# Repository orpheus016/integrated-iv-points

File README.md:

# four-point-probe
Four point probe for semiconductor instrumentation system

## Software: voltage simulation pipeline

This repo includes a modular Python simulation for voltage acquisition with
filters, live plotting, and CSV logging. It is designed to be swapped later with
ADS1256 serial input from Arduino.

## Development

If you plan to change code, start with:

- [CONTRIBUTING.md](CONTRIBUTING.md) for the CI contract, local preflight, and PR checklist.
- [software/scripts/README.md](software/scripts/README.md) for `evaluate`, `integrate`, and the compliance checker.
- [software/README.md](software/README.md) for the software module overview and run examples.
- `CONTRIBUTING.md` also explains how to write new tests under `software/tests/` and run them from the repo root.

### Setup

Install dependencies:

```bash
pip install matplotlib
```

Optional (for future ADS1256 serial input):

```bash
pip install pyserial
```

### Run

From the repo root:

```bash
python -m software.main
```

Example with custom settings:

```bash
python -m software.main --sample-rate 100 --window-seconds 8 --noise 0.0005 --step
```

## Offline data paths

There are two ways to work with recorded CSV data:

1. Replay a CSV through the live runtime when you want the same pipeline as hardware, including the backbone, logger, and visualizer:

```bash
python -m software.main --source csv --csv-path software/output/testbench/stable20mA.csv --backbone baseline
```

2. Run offline evaluation when you want metrics and snapshot comparison without hardware commands or the live plot loop:

```bash
python -m software.scripts.evaluate --input software/output/testbench/stable20mA.csv --backbones baseline --out software/output/evaluate/baseline-stable20mA
```

The offline evaluator writes a metrics CSV with the decided snapshot fields, marks that chosen snapshot with a star in the plot, and keeps the result separate from the live runtime output.

The default snapshot recording gate is configured in [software/config/config.py](software/config/config.py), including the minimum recording duration used before a backbone may decide on a VI snapshot.

## Serial protocol and CLI

Hardware integration uses a small text protocol implemented by the Arduino firmware and
managed by `software/command/serial_commander.py`.

Framing markers (exact strings):

- `*STREAM_START` — emitted by the Arduino to mark stream beginning
- `*STREAM_STOP` — emitted by the Arduino to mark stream termination

Control commands sent from host to Arduino (single ASCII characters):

- `R` — reset device
- `C` — start streaming samples
- `s` — stop streaming
- `iN` — set current stage to `N` (e.g. `i2`)

The serial reader expects CSV-style measurement lines containing `voltage,current_mA`.

Common CLI execution examples:

- Replay testbench CSVs and write evaluation results:
	python -m software.scripts.evaluate --input software/output/testbench --out results/

Single backbone on single dataset (example):
	python -m software.scripts.evaluate \
		--input software/output/testbench/stable20mA.csv \
		--backbones baseline \
		--out results/single_baseline_stable20mA
- Run main with hardware ADS1256 on COM5:
	python -m software.main --source serial --port COM5 --baud 115200 --backbone baseline
- Run headless evaluation from Python:
	python -c "from software.scripts.evaluate import main; main(['--input','software/output/testbench'])"

See `software/config/config.py` for all CLI defaults and flags (backbone selection, hysteresis thresholds, plot mode, etc.).

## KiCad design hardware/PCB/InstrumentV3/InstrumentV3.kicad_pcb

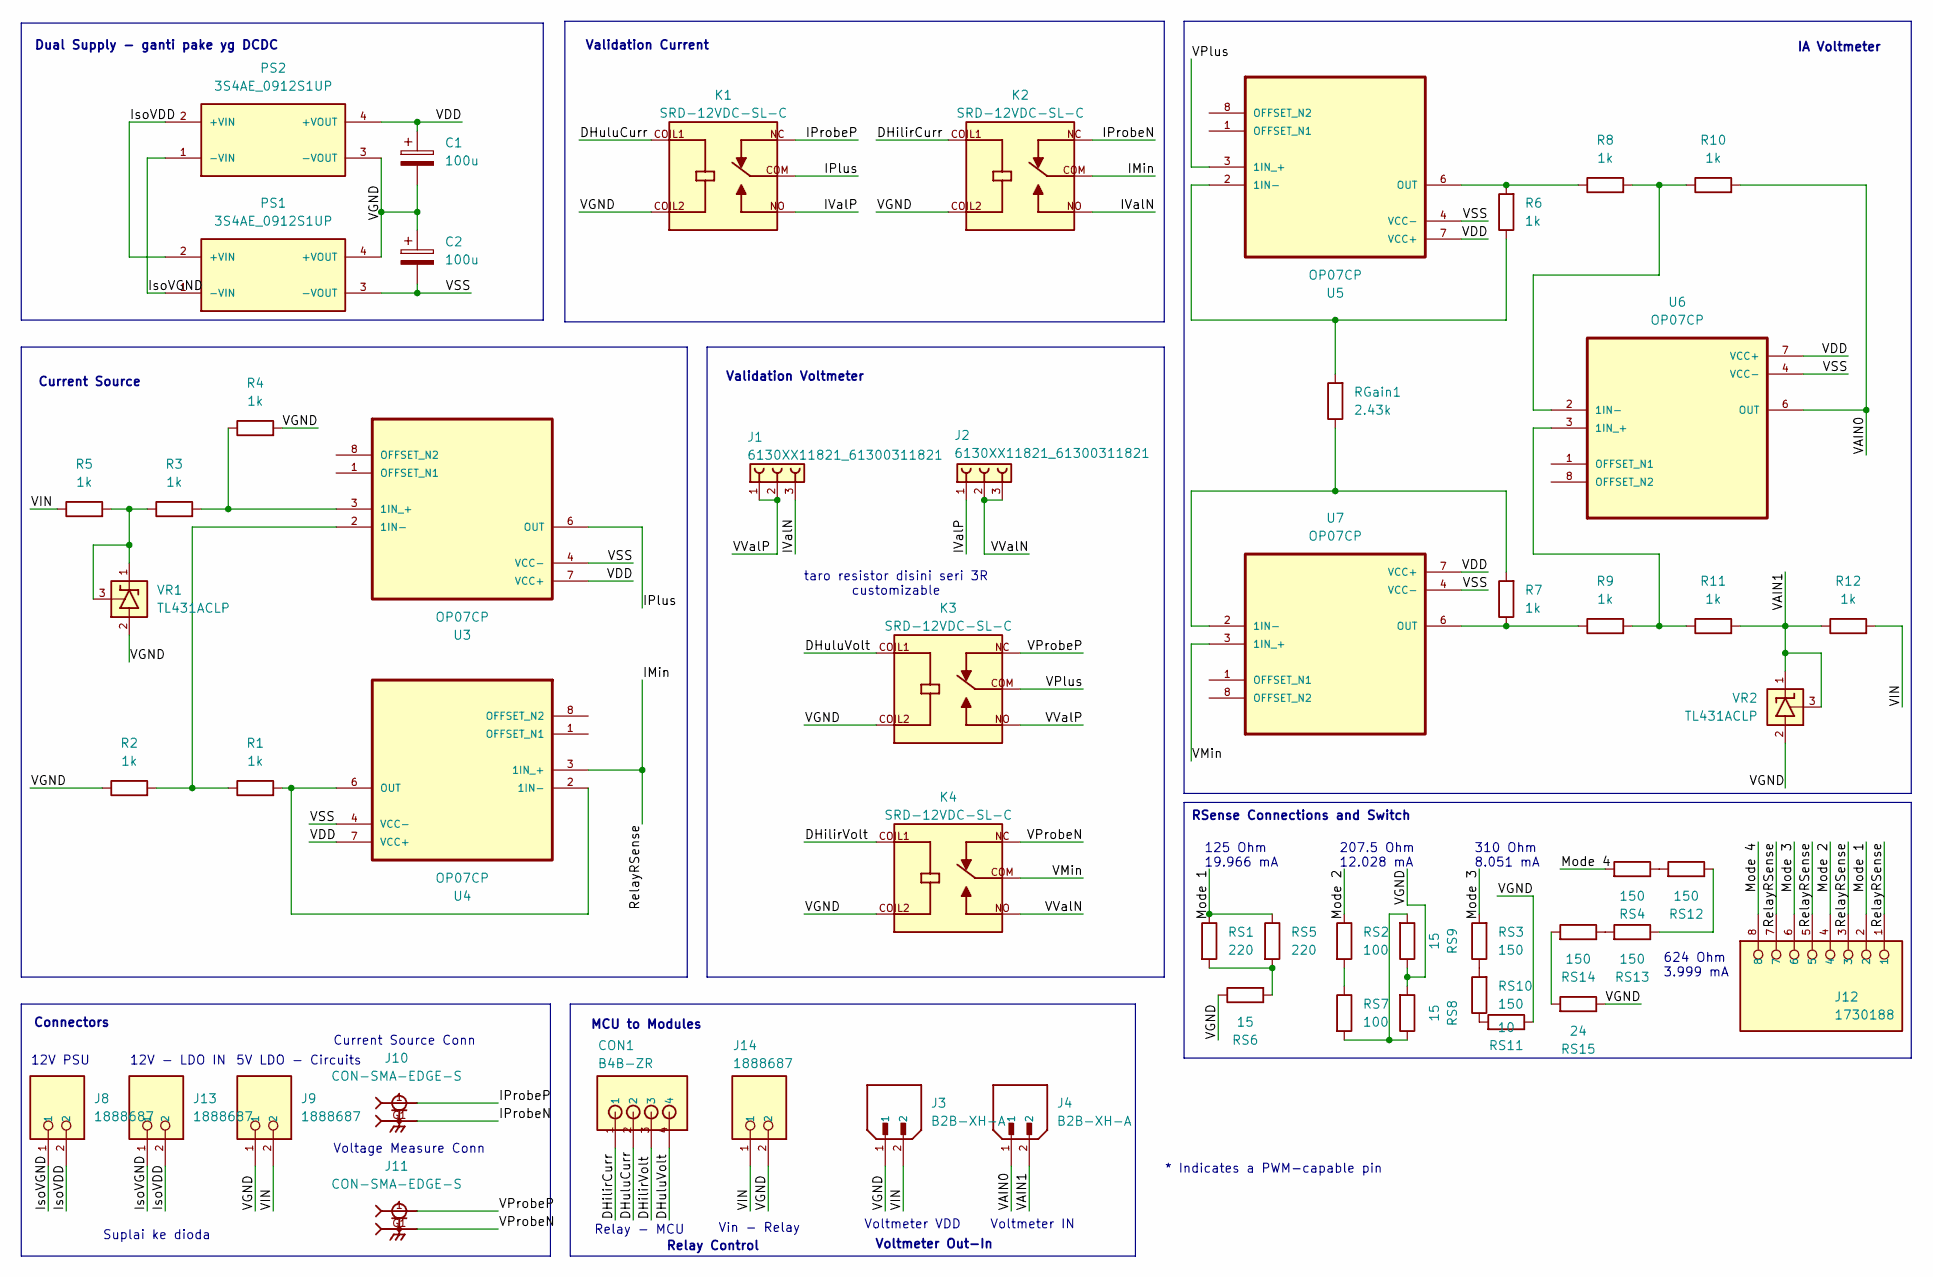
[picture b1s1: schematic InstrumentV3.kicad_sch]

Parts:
C1, C2: 100u; CP_Radial_D6.3mm_P2.50mm
CON1: B4B-ZR
J1, J2: 6130XX11821_61300311821; 61300311821
J3, J4: B2B-XH-A; JST_B2B-XH-A; PARTREV N/A
J8, J9, J13, J14: 1888687; PHOENIX_1888687; PARTREV 26.09.2015
J10, J11: CON-SMA-EDGE-S; RFSOLUTIONS_CON-SMA-EDGE-S; PARTREV 1
J12: 1730188; PHOENIX_1730188
K1, K2, K3, K4: SRD-12VDC-SL-C; RELAY_SRD-12VDC-SL-C; PARTREV 1.0
PS1, PS2: 3S4AE_0912S1UP; CONV_3S4AE_0912S1UP; PARTREV 2019-1.0
R1, R2, R3, R4, R5, R6, R7, R8, R9, R10, R11, R12: 1k; R_0603_1608Metric_Pad0.98x0.95mm_HandSolder
RGain1: 2.43k; R_0805_2012Metric_Pad1.20x1.40mm_HandSolder
RS1, RS5: 220; R_0603_1608Metric_Pad0.98x0.95mm_HandSolder
RS2, RS7: 100; R_1206_3216Metric_Pad1.30x1.75mm_HandSolder
RS3, RS4, RS10, RS12, RS13, RS14: 150; R_0805_2012Metric_Pad1.20x1.40mm_HandSolder
RS6, RS8, RS9: 15; R_0603_1608Metric_Pad0.98x0.95mm_HandSolder
RS11: 10; R_0805_2012Metric_Pad1.20x1.40mm_HandSolder
RS15: 24; R_0805_2012Metric_Pad1.20x1.40mm_HandSolder
U3, U4, U5, U6, U7: OP07CP; DIP794W45P254L959H508Q8
VR1, VR2: TL431ACLP; VREG_TL431ACLP; PARTREV R

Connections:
/DHilirCurr: CON1.1, K2.COIL1
/DHilirVolt: CON1.3, K4.COIL1
/DHuluCurr: CON1.2, K1.COIL1
/DHuluVolt: CON1.4, K3.COIL1
/IMin: J12.1, J12.3, J12.5, J12.7, K2.COM, U4.3 (1IN_+)
/IPlus: K1.COM, U3.6 (OUT)
/IProbeN: J10.G1, J10.G2, J10.G3, J10.G4, K2.NC
/IProbeP: J10.1, K1.NC
/IValN: J1.3, K2.NO
/IValP: J2.1, K1.NO
/IsoVDD: J8.2, J13.2, PS1.2 (+VIN), PS2.2 (+VIN)
/IsoVGND: J8.1, J13.1, PS1.1 (-VIN), PS2.1 (-VIN)
/Mode 1: J12.2, RS1.1, RS5.1
/Mode 2: J12.4, RS2.1
/Mode 3: J12.6, RS3.2
/Mode 4: J12.8, RS4.2
/VAIN0: J4.1, R10.2, U6.6 (OUT)
/VAIN1: J4.2, R11.2, R12.1, VR2.1, VR2.3
/VDD: C1.1, PS2.4 (+VOUT), U3.7 (VCC+), U4.7 (VCC+), U5.7 (VCC+), U6.7 (VCC+), U7.7 (VCC+)
/VGND: C1.2, C2.1, J3.1, J9.1, J14.2, K1.COIL2, K2.COIL2, K3.COIL2, K4.COIL2, PS1.4 (+VOUT), PS2.3 (-VOUT), R2.1, R4.2, RS6.1, RS8.2, RS9.1, RS11.1, RS15.1, VR1.2, VR2.2
/VIN: J3.2, J9.2, J14.1, R5.1, R12.2
/VMin: K4.COM, U7.3 (1IN_+)
/VPlus: K3.COM, U5.3 (1IN_+)
/VProbeN: J11.G1, J11.G2, J11.G3, J11.G4, K4.NC
/VProbeP: J11.1, K3.NC
/VSS: C2.2, PS1.3 (-VOUT), U3.4 (VCC-), U4.4 (VCC-), U5.4 (VCC-), U6.4 (VCC-), U7.4 (VCC-)
/VValN: J2.2, J2.3, K4.NO
/VValP: J1.1, J1.2, K3.NO
unnamed: R3.1, R5.2, VR1.1, VR1.3
unnamed: RS1.2, RS5.2, RS6.2
unnamed: RS2.2, RS7.1
unnamed: RS7.2, RS8.1, RS9.2
unnamed: RS10.1, RS11.2
unnamed: RS3.1, RS10.2
unnamed: RS12.1, RS13.1
unnamed: RS4.1, RS12.2
unnamed: RS13.2, RS14.1
unnamed: RS14.2, RS15.2
unnamed: R1.1, R2.2, U3.2 (1IN-)
unnamed: R3.2, R4.1, U3.3 (1IN_+)
unnamed: R1.2, U4.2 (1IN-), U4.6 (OUT)
unnamed: R6.1, RGain1.2, U5.2 (1IN-)
unnamed: R6.2, R8.1, U5.6 (OUT)
unnamed: R8.2, R10.1, U6.2 (1IN-)
unnamed: R9.2, R11.1, U6.3 (1IN_+)
unnamed: R7.2, RGain1.1, U7.2 (1IN-)
unnamed: R7.1, R9.1, U7.6 (OUT)

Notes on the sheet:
624 Ohm 3.999 mA
Voltmeter Out-In
Voltmeter VDD
Relay Control
Connectors
Suplai ke dioda
IA Voltmeter
5V LDO - Circuits
Validation Voltmeter
Validation Current
taro resistor disini seri 3R customizable
310 Ohm 8.051 mA
12V - LDO IN
Current Source Conn
12V PSU
Dual Supply - ganti pake yg DCDC
Current Source
125 Ohm 19.966 mA
Relay - MCU
* Indicates a PWM-capable pin
Voltage Measure Conn
207.5 Ohm 12.028 mA
Vin - Relay
Voltmeter IN
RSense Connections and Switch
MCU to Modules

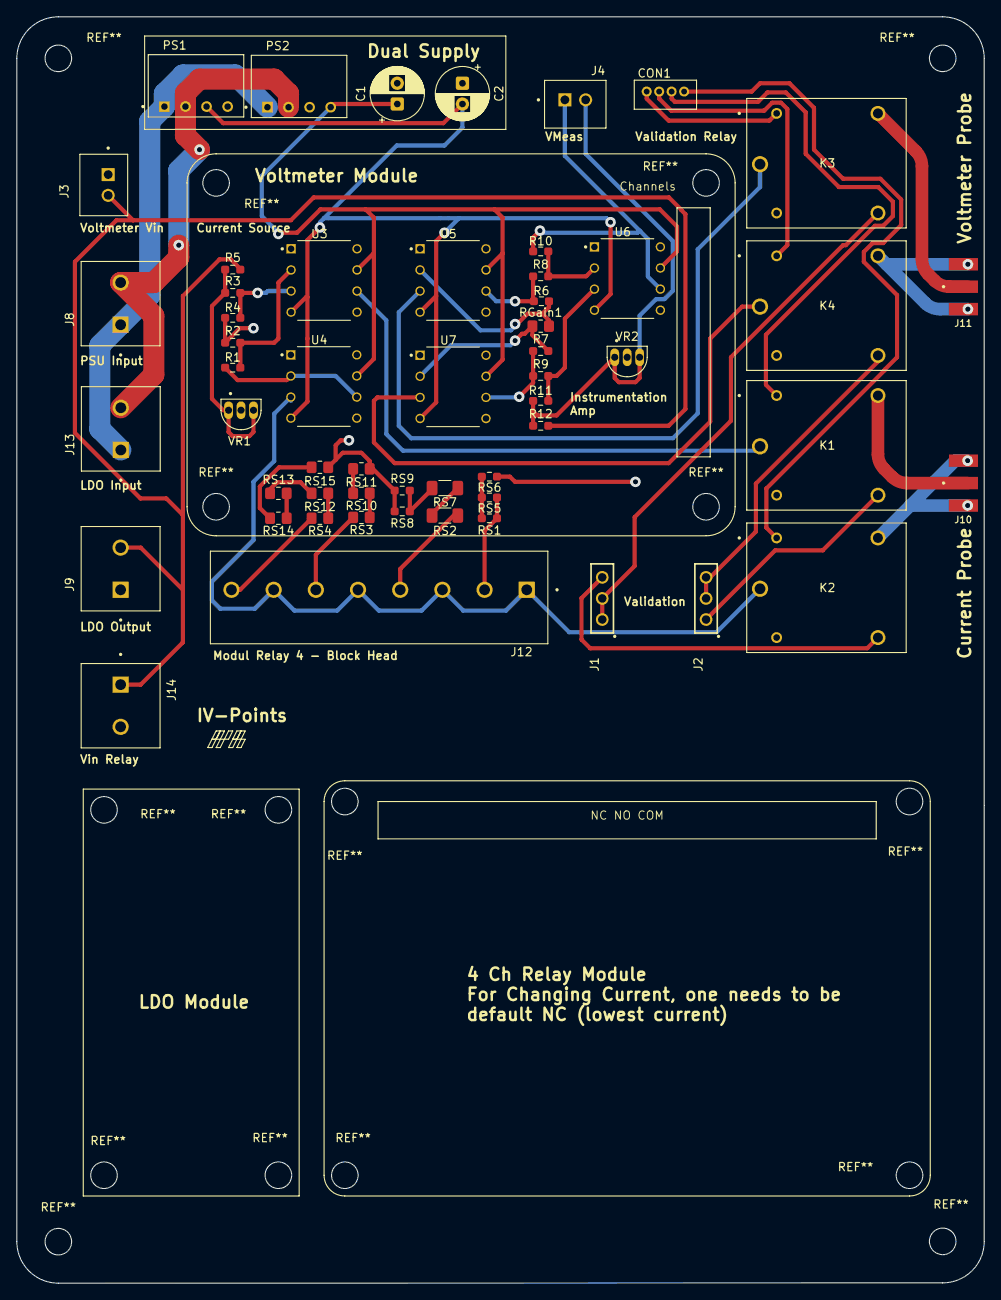
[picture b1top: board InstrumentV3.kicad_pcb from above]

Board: 2 copper layers, 116.5 x 152.5 mm, 55 parts (0 on the bottom side), 47 nets.

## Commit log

2026-06-19 add: integration
2026-06-19 fix: integration
2026-06-19 fix: loading page frontend bridge
2026-06-19 restore: frontend
2026-06-19 task: test integration pls
2026-06-19 fix: backend integration
2026-06-19 add: output log
2026-06-19 test: voltage gain on loading and result page
2026-06-19 test: snapshot on frontend
2026-06-19 test: current switching
2026-06-20 fix: prefix
2026-06-20 output: current switching
2026-06-20 test: sample rate
2026-06-20 add: log
2026-06-21 test: reset to 4mA
2026-06-21 test: vi snapshot from backend
2026-06-21 test: mlx auto
2026-06-21 add: lod
